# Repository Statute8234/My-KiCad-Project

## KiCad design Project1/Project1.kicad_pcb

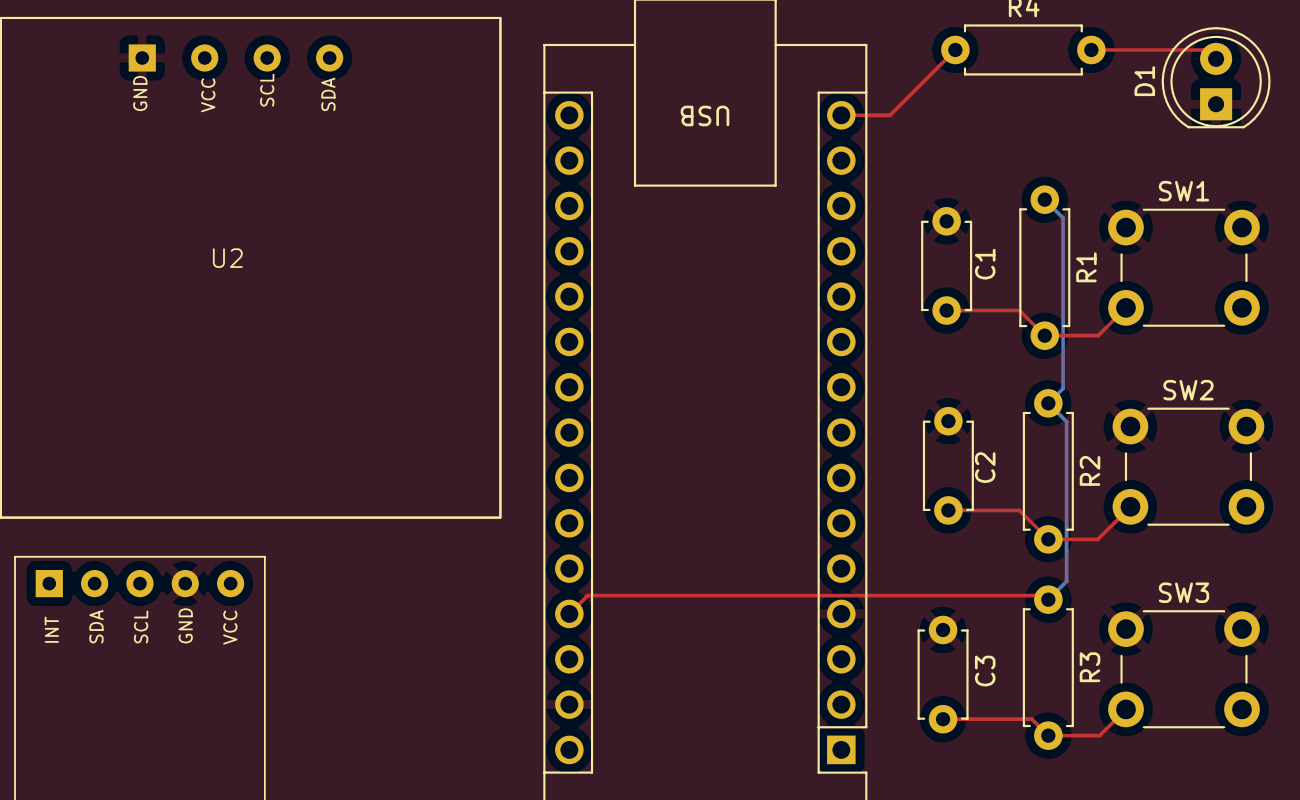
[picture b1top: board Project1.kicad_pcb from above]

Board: 4 copper layers, 14 parts (0 on the bottom side), 9 nets.

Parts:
A1: Arduino_Nano_v3.x; Arduino_Nano
C1, C2, C3: 100n; C_Disc_D4.7mm_W2.5mm_P5.00mm
D1: LED; LED_D5.0mm
R1, R2, R3, R4: 1k; R_Axial_DIN0207_L6.3mm_D2.5mm_P7.62mm_Horizontal
SW1, SW2, SW3: SW_Push; SW_PUSH_6mm
U1: MAX30102; MAX30102_MODULE
U2: SSD1306

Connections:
+5V: A1.27 (+5V), R1.1, R2.1, R3.1, U1.5 (VCC)
GND: A1.4 (GND), A1.29 (GND), C1.2, C2.2, C3.2, D1.1 (K), SW1.1, SW2.1, SW3.1, U1.4 (GND), U2.1 (GND)
unnamed: A1.23 (A4), U1.2 (SDA), U2.4 (SDA)
unnamed: A1.24 (A5), U1.3 (SCL), U2.3 (SCL)
unnamed: A1.5 (D2), C3.1, R3.2, SW3.2
unnamed: A1.6 (D3), C2.1, R2.2, SW2.2
unnamed: A1.7 (D4), C1.1, R1.2, SW1.2
unnamed: A1.15 (D12), R4.1
unnamed: D1.2 (A), R4.2

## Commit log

2024-09-15 Inital commit
2024-09-16 Finished with my first porject
2024-09-16 Adding footprints
2024-09-19 Finxing the full progect
2024-10-27 Complete
